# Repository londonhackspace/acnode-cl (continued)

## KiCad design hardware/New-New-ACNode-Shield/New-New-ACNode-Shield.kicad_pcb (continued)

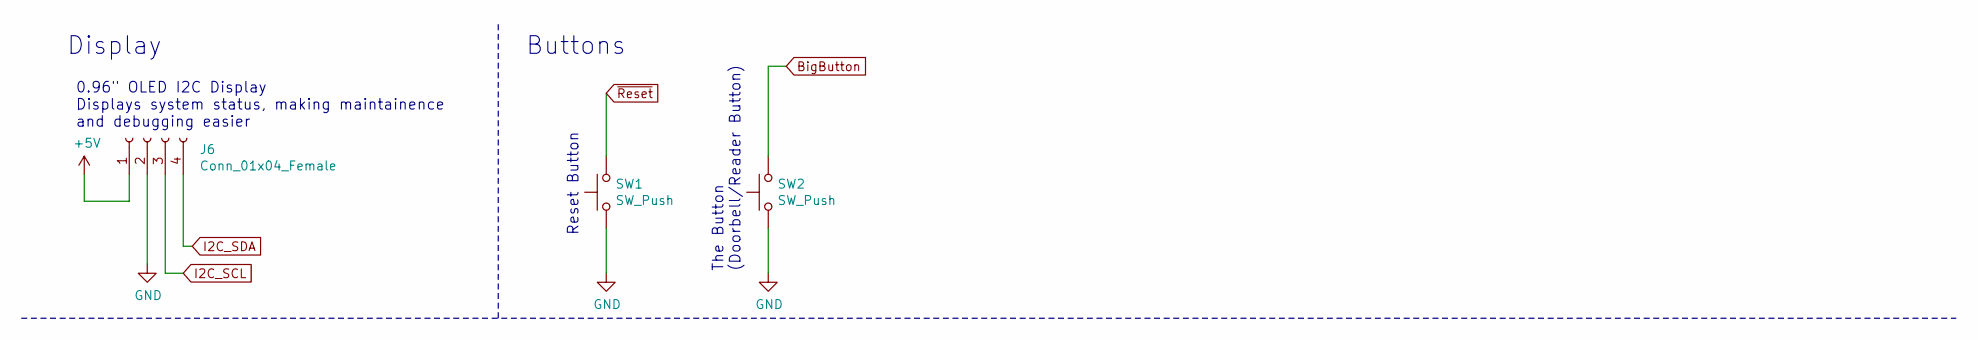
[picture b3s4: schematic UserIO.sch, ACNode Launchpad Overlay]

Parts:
J6: Conn_01x04_Female; PinHeader_1x04_P2.54mm_Vertical
SW1, SW2: SW_Push; SW_PUSH_6mm

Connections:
+5V: J6.1; also elsewhere on the board
BigButton: SW2.2; also elsewhere on the board
GND: J6.2, SW1.1, SW2.1; also elsewhere on the board
I2C_SCL: J6.3; also elsewhere on the board
I2C_SDA: J6.4; also elsewhere on the board
~Reset: SW1.2; also elsewhere on the board

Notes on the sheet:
Display
0.96" OLED I2C Display Displays system status, making maintainence and debugging easier
Buttons
Reset Button
The Button (Doorbell/Reader Button)

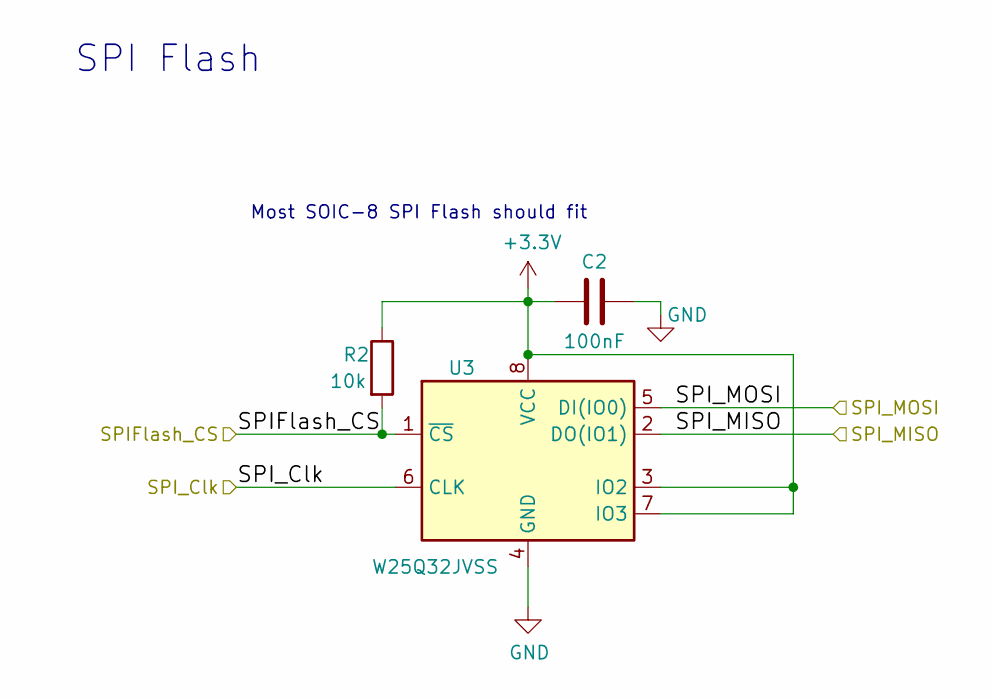
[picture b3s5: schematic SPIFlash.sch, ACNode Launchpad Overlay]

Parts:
C2: 100nF; C_0603_1608Metric
R2: 10k; R_0603_1608Metric
U3: W25Q32JVSS; SOIC-8_5.23x5.23mm_P1.27mm

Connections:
+3V3: C2.2, R2.1, U3.3 (IO2), U3.7 (IO3), U3.8 (VCC); also elsewhere on the board
/SPIFlash_CS: R2.2, U3.1 (~CS); also elsewhere on the board
/SPI_Clk: U3.6 (CLK); also elsewhere on the board
/SPI_MISO: U3.2 (DO(IO1)); also elsewhere on the board
/SPI_MOSI: U3.5 (DI(IO0)); also elsewhere on the board
GND: C2.1, U3.4 (GND); also elsewhere on the board

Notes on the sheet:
Most SOIC-8 SPI Flash should fit
SPI Flash

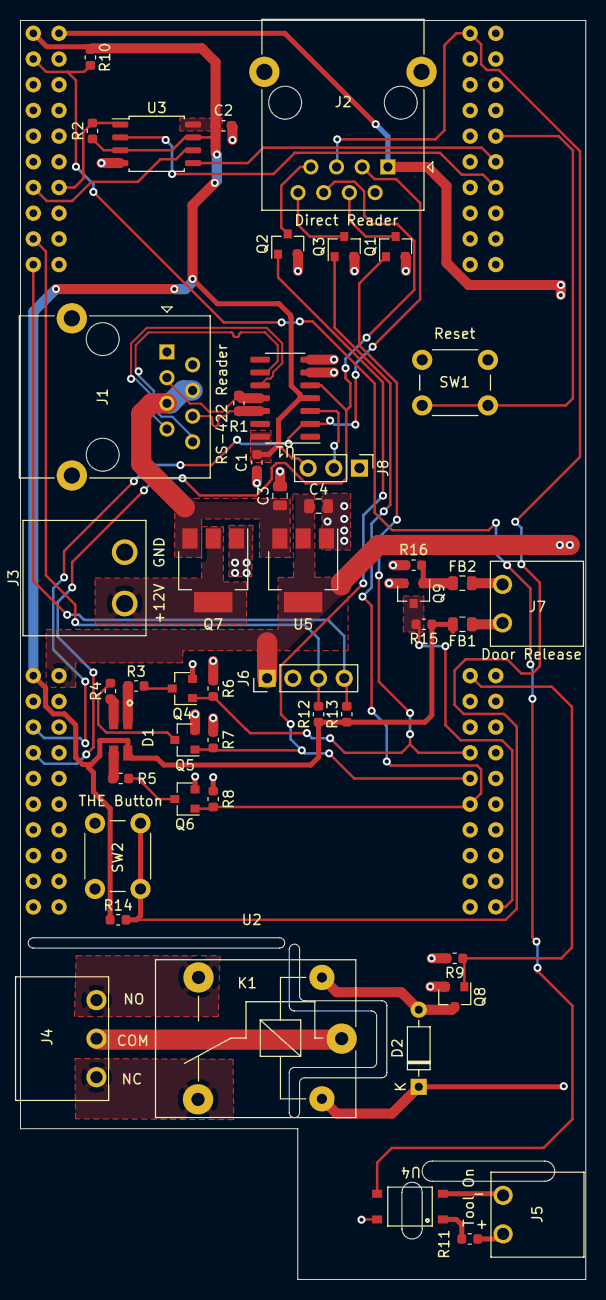
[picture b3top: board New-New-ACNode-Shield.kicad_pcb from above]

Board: 2 copper layers, 55.9 x 124.5 mm, 49 parts (0 on the bottom side), 45 nets.

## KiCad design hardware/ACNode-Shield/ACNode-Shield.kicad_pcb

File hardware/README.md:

# How to make an ACnode or Doorbot

Over the years the design of the ACnodes and doorbots have been gradually improved.

As of 2021-10-28, all acnodes and doorbots in London Hackspace have been using the 'New-ACNode-Doorbot-Shield' designs. This is a single PCB designed to
fit **underneath** a TI Tiva C XL Connected Launchpad microcrontroller board EK-TM4C1294XL EVAL BRD, TIVA C CONNECTED LAUNCHPAD. The Launchpad boards are normally available from Farnell and RS.

There are plans for an all-new doorbot/acnode board together with a reader module, but they are not as yet ready for use. This is to address interference on long cable runs between the acnode/doorbot board and reader.

The board features an on-board 5V coil relay that is suitable for switching up to 10A of 230V. If you need to switch anything greater, then use it to
energise the coil of an appropriate contactor.

Build up the ACnode board as per kicad schematics. On rev 1.1b, component values are silkscreened for easy assembly. You will require long header pins so that the Launchpad board sits above the relay. Hint when soldering the long header pins into this board - use a Launchpad upside-down as a jig to hold the pins, place the pins, place the ACnode board upside-down, then solder them. Once soldered, a blob of hot glue is advised to keep the long header pins spaced and prevent bending them when handling in future.
When building the board for the ACnode role, you may omit the LM7805 voltage regulator if you're only going to be providing it with +5V power.

Always ensure that any metal enclosure is suitably earthed.

## Doorbot role

You will require

- A +12V power supply, approximately 3A at 12V should be enough to energise a maglock or solenoid lock. You can't use POE for this, it won't provide enough current for a maglock.
- Optional: A sealed lead acid battery, recommended for exterior doors. The doorbot software is designed to handle power outages with no networking available.
- A suitable helpfully labelled DOOR EXIT button, SPDT or DPDT, must be able to handle the current of whatever lock you choose. We will use two poles to both interrupt the current to the lock (NC contact) and to signal the doorbot to hold the door open for a time.
- Some CAT5 or higher wiring and connectors to run a cable to the reader module.
- Some suitable wire. We've found that old +12V DC power cables for CCTV cameras is suitable for the 12V lock circuit.
- A suitable enclosure
- A micro-USB to laptop cable, of suitable length, for configuration and flashing the software.
- A maglock with bracket, or solenoid deadbolt. 12V DC.

## ACnode role

You will require

- A +5V power supply, most decent USB power supplies work well, and you can get POE splitters that will provide this via Micro USB as well. Most of the London Hackspace network switches support POE. This is normally the recommended solution.
- Some CAT5 or higher wiring and connectors to run a cable to the reader module.
- Knowledge of the tool that you are providing access control to. Ideally, you'd be switching a low(er) voltage control circuit like an e-stop, rather than turning full power on and off to the tool. For high current switching, use an external suitably sized mains contactor.
- optional: a tool-running input, like on the laser cutter, the AC node can log the time the tool was running.
- suitable enclosure, or suitable space within the tool for the board. DIN rail mounting is recommended, 3D printed DIN-rail clips have been known to work with the board glued to the clips. Where we need a standalone enclosure, we have used TA 241911 ENCLOSURE BOX, GREY, IP65, 240X191X107MM, Farnell Part number 1422671
- A micro-USB to laptop cable, of suitable length, for configuration and flashing the software.

Set the power select jumper on the Launchpad board to 'OTG', and plug your USB power supply into the 'OTG' interface, we'll use that to provide power to the microcontroller.

## Reader enclosure

Typically used for ACnode roles.
Can use any suitable enclosure, but ideally one deep enough for the arcade button, and a RJ45 modular connector. https://uk.farnell.com/schneider-electric/dpn10-10/box-abs-103x103x56mm/dp/161706 has worked well.
For a laser-cut card holder front-end, see the dxf files in this repository's hardware/ directory. These will need M2.5 nylon nuts to hold the stack of laser cut acrylic together through to the front cover of the reader.
We have typically used arcade microswitch buttons with LED. " Ultralux RGB Illuminated Arcade Button " from Arcade World UK. https://www.arcadeworlduk.com/products/ultralux-rgb-illuminated-arcade-button.html

For doorbot roles, we typically build the readers into standard socket boxes with blanking plates. Exterior card readers will need a suitably watertight enclosure with a watertight button.
Drilling a standard EN 60670-1 thermosetting plastic blanking plate to fit LED and buttons makes them prone to cracking. Start with a tiny pilot drill, ideally in a drill press, and work up sizes. Fortunately, they are cheap and very easy to come by (wilko,screwfix,B&Q).
RJ45 termination to a modular jack is typically within the enclosure rather than external as on most of the acnode role readers.
PN532 RFID reader module: Set to HSS mode. Elechouse V4. Order direct from Elechouse. Do not skimp on ordering from aliexpress or ebay, because there are huge numbers of clones with AWFUL antenna matching circuitry.

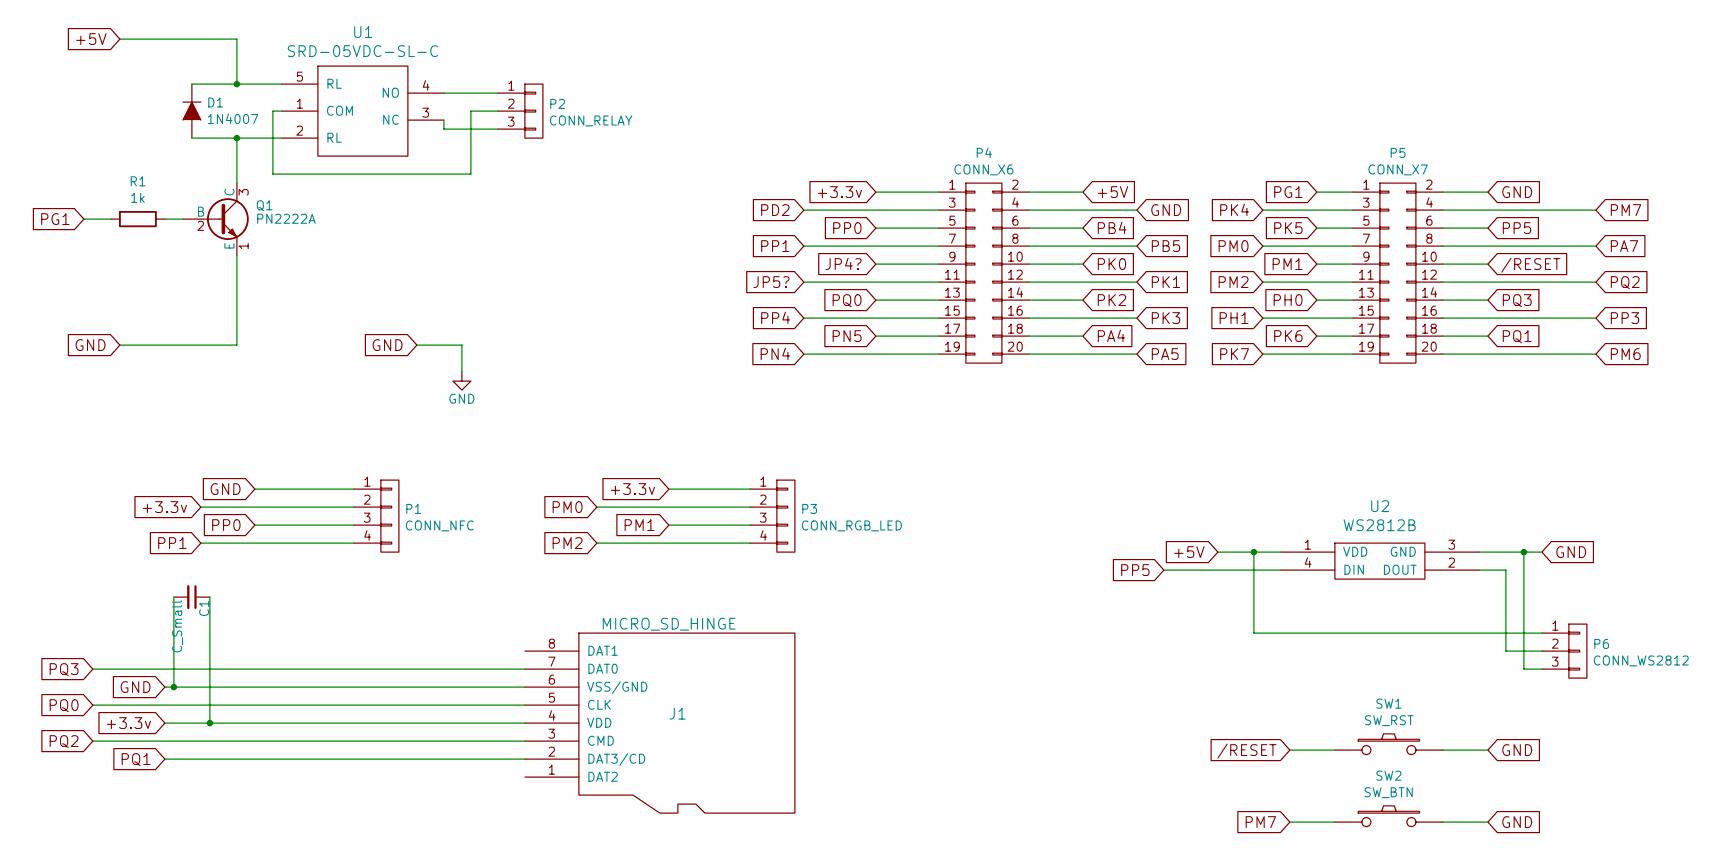
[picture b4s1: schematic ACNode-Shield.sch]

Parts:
C1: C_Small; C_1206
D1: 1N4007; Diode_DO-41_SOD81_Horizontal_RM10
J1: MICRO_SD_HINGE; MicroSD_Slot
P1: CONN_NFC; Pin_Header_Straight_1x04
P2: CONN_RELAY; TerminalBlock_Pheonix_MKDS1.5-3pol
P3: CONN_RGB_LED; Pin_Header_Straight_1x04
P4: CONN_X6; Socket_Strip_Straight_2x10
P5: CONN_X7; Socket_Strip_Straight_2x10
P6: CONN_WS2812; Pin_Header_Straight_1x03
Q1: PN2222A; TO-92_Inline_Wide
R1: 1k; Resistor_Horizontal_RM10mm
SW1: SW_RST; SW_PUSH_SMALL
SW2: SW_BTN; Socket_Strip_Straight_1x02
U1: SRD-05VDC-SL-C; Relay_SANYOU_SRD_Series_Form_C
U2: WS2812B; WS2812b

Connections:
+3.3v: C1.1, J1.4 (VDD), P1.2, P3.1, P4.1
+5V: D1.1 (K), P4.2, P6.1, U1.5 (RL), U2.1 (VDD)
/RESET: P5.10, SW1.1
GND: C1.2, J1.6 (VSS/GND), P1.1, P4.4, P5.2, P6.3, Q1.1 (E), SW1.2, SW2.2, U2.3 (GND)
JP4?: P4.9
JP5?: P4.11
unnamed: D1.2 (A), Q1.3 (C), U1.2 (RL)
unnamed: P2.1, U1.4 (NO)
unnamed: P2.2, U1.1 (COM)
unnamed: P2.3, U1.3 (NC)
unnamed: P6.2, U2.2 (DOUT)
unnamed: Q1.2 (B), R1.1
PA4: P4.18
PA5: P4.20
PA7: P5.8
PB4: P4.6
PB5: P4.8
PD2: P4.3
PG1: P5.1, R1.2
PH0: P5.13
PH1: P5.15
PK0: P4.10
PK1: P4.12
PK2: P4.14
PK3: P4.16
PK4: P5.3
PK5: P5.5
PK6: P5.17
PK7: P5.19
PM0: P3.2, P5.7
PM1: P3.3, P5.9
PM2: P3.4, P5.11
PM6: P5.20
PM7: P5.4, SW2.1
PN4: P4.19
PN5: P4.17
PP0: P1.3, P4.5
PP1: P1.4, P4.7
PP3: P5.16
PP4: P4.15
PP5: P5.6, U2.4 (DIN)
PQ0: J1.5 (CLK), P4.13
PQ1: J1.2 (DAT3/CD), P5.18
PQ2: J1.3 (CMD), P5.12
PQ3: J1.7 (DAT0), P5.14

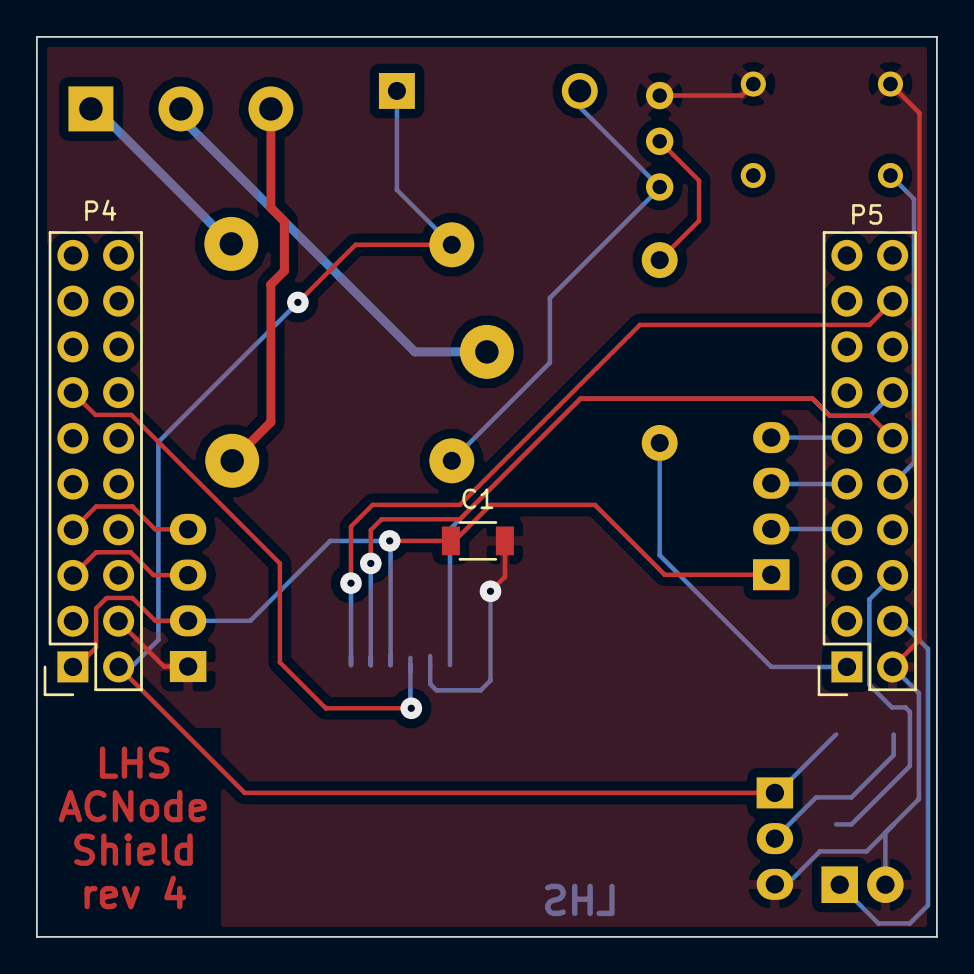
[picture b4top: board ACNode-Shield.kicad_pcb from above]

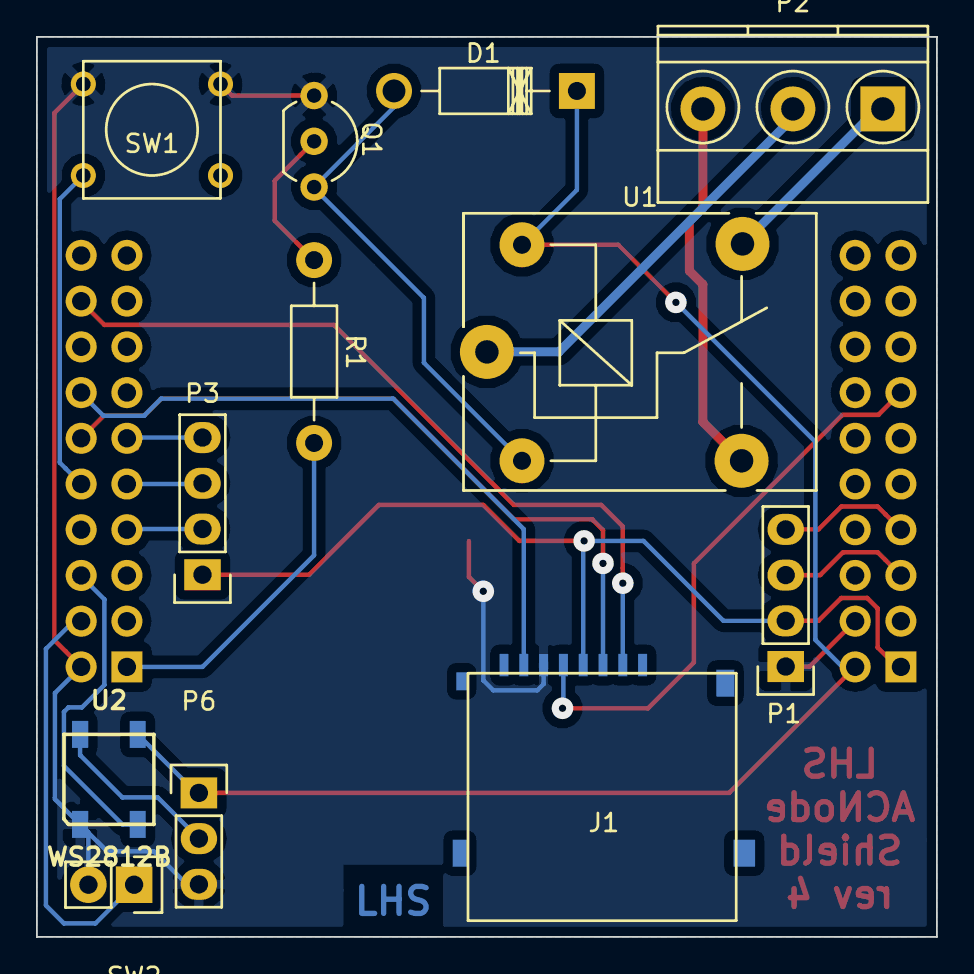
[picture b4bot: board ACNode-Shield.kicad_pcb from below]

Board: 2 copper layers, 50.0 x 50.0 mm, 15 parts (12 on the bottom side), 22 nets.

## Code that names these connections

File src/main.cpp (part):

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
Every am_i_alive(60000);

#define BUTTON_PIN PF_1
#define DOOR_RELEASE_PIN PM_6
#define SD_CS_PIN PC_7
#define ACNODE_DIR "ACNODE"

void serviceLed() { rgb.run(); };
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
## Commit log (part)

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2014-10-02 add a nice cli library (microrl, LGPLv3), add support for saving settings in the eeprom and editing them via the cli
2014-10-02 add support for saving status in the settings
2014-10-02 only count valid users
2014-10-07 get the mac address from the user registers, fixes #7, and fix a few more warnings
2014-10-07 a bit more helpful help
2014-10-09 also print the port
2014-10-10 only allow maintainers to run a tool if it's out of service.
2014-10-10 make the docs make a bit more sense
2014-11-13 add rgb support, reduce the grace period (it was annoyingly long)
2014-11-28 useful debugging thing
2014-11-28 Use a short timeout and the new PN532 powerdown thing so we can poll things faster.
    Use Every to not print debug out everytime.
    Still a work in progress, N.B. new version of the PN532 code needed (just git pull it).
2014-12-01 move the code that we call when we have a valid card code to it's own function.
    tidy things up a bit
    timeout adding a new card rather than waiting for ever.
    handle led's a bit better.
2014-12-03 keep state of what colour we are to avoid more flickering
2014-12-04 debounce a bit since we now sample the button much more often
2014-12-04 formatting
2014-12-14 switch the tool off when it is marked as out of service, bump to beta 2
2014-12-23 don't try to swith the tool on if it's out of service
2014-12-23 how to make the transistor switch and wire in the button
2014-12-29 poke the acserver with the tool run time
2014-12-31 better formatting
2015-02-19 if the board does not have valid settings, save the default ones. For some reason this makes the card reader work :/ see issue #15
2015-05-09 don't update the tool status on error
2015-05-09 print out the code version in a few places
2015-08-27 Door class for opening and closing the door.
2015-09-04 The SD card library is now found by Energia's compiler.
2015-09-05 Replaced code in user.cpp with calls to the SD card cache.
2015-09-08 toolUse is not used so remove it, fixes issue #31
2015-09-09 verify the user cache on startup (and with a command), closes #32
2015-09-10 Open door if a known card is presented. Parse numbers in http response, rather than a single digit. No caching at the moment.
2015-09-11 Add watchdog support, closes #17
2015-09-11 add a changelog
2015-09-12 add minimum on time support, closes #22
2015-09-12 bump version
2015-09-14 user.h -> card.h, bump version too
2015-09-15 get_user -> cache->get most of class Card, rest of code not converted yet
2015-09-22 add a cache type setting change some details in the settings struct - nodeid is now 16 bits upgrade settings if old settings found
2015-09-23 Fix issue with all cards appearing to have a long uid
2015-09-23 feed the watchdog in Cache::each
2015-09-24 more detail on hooking up an sdcard, add a cli command to change which cache to use
2015-09-26 Warn if the tool starts or stops running when it is switched off, fixes #37
2015-10-07 terminate the ret buffer to avoid printing junk when the network is down
2015-10-11 fix eepromcache not caching things
2015-11-05 Add an additional pin, negated, for use with a different type of a relay.
2016-04-12 Symbolic links to subtree'd PN532 library.
2016-04-12 Moved hardware directory to the root.
2016-04-12 Squashed 'lib/Syslog/' content from commit 1a11d1c
    git-subtree-dir: lib/Syslog
    git-subtree-split: 1a11d1cfe95d625688d14112cdd93d7c7566f6c3
2016-04-13 PlatformIO now has the latest Energia, but it still doesn't solve our problem with the SPI library.
2016-04-14 README
2016-04-18 Updated build recipe for travis. sigh.
2016-04-29 Added a pinout of the board in high res.
2016-05-07 PCB rev 1
2016-05-12 Removed a resistor, fixed some tracks.
2016-05-14 Removed old outputs.
2016-05-15 Design was mirrored, need to redo this whole thing from scratch.
2016-07-09 Don't die when there's no SD card connected.
2016-07-10 DRY, introduce timeout handling.
2016-07-10 Feed watchdogs here and there.
2016-07-10 Basic doorbot (1) now works.
2016-07-10 Announcing works, need to add card debouncing (?).
2016-07-10 Further changes - see last commit.
2016-07-10 Created a superclass with common logic, called Role.
2016-07-10 Fixed namespaced identifiers.
2016-07-11 "secret none" disables the secret key.
2016-09-29 I've made the component pads thicker, for easier soldering.
2016-10-04 Added some text on copper layers.
2016-11-04 Removed a single trace that wasn't needed.
2016-11-07 Very basic access control for the acnode - inefficient but simple.
2016-11-12 Got the LED to flash nicely.
2016-11-13 RGB class supports two-colour flashing. A maintainer can take a tool online and offline. When activated by a maintainer the LED turns yellow, when by a user - green.
2016-11-13 Correct colouring based on different user types.
2016-11-13 Tell acserver when the tool is in use.
2016-11-15 When retrieving a valid entry, bump the entry's expiration timestamp.
2016-11-17 If a card is cached already, don't add another entry.
2016-11-17 Tiny fix.
2016-11-23 Reversed contacts on the SD card connector - it should work now.
    Bumped revision of the board to 4.
2017-05-10 Added a rainbow cycle during bootup as a quick check if the LED is working.
    This relies on working OneMsTaskTimer.cpp implementation for which there will be a PR for in Energia.
2017-05-16 Folded user agent into a compile-time define.
2017-05-20 Check if tool is enabled, every 30 seconds - force-checking when disabled every 500ms doesn't make sense. The led lights up as red when it is out of order.
2017-05-20 Fix failing build. Included a patch that enables OneMsTaskTimer, a timer-based ticker for automatically updating the LED.
2018-08-04 Fixed build
2018-08-07 Fix key length in settings.cpp
2018-08-26 Add MQTT Announcer
    Added first pass at an MQTT announcer
2018-08-27 Turns out for reliable MQTT we need to yield regularly
2018-09-04 correct pin for DOOR_RELEASE_PIN
2018-09-08 bug on the popular AC node rev 2.0 board means that button_pin is now PF_1 instead of PM_7
2018-11-03 Modify RFID announcement over mqtt to include whether access was granted, or not.
2018-11-05 improve header file to reduce warnings at compile time
2018-11-24 Fix a couple of buffer overruns in the MQTT code
    One was the template class for the MQTT client was set to a maximum length of 50 bytes,
    which is shorter than most of our messages. The other was a more subtle one where the
    card buffer didn't have room for a null terminator.
2018-12-03 quick change of documentation, some clarification
2019-02-15 From Liam: The RFID card holders to be lasercut to hold the cards in the readers.
2019-02-28 fix bug where the verify() call wasn't actually touching datestamp in ramcache.
2019-03-01 Improve cacheing refresh, implement colour code MAUVE that means that the card has been read, and it's waiting on a network response. If this colour stays on, it means that there's a networking probl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
2019-03-10 Make more robust in cases of network link failure
    When the network link goes down, the doorbot tries
    to do stuff anyway, which results in a generally nasty situation
    where it will probably hit enough timeouts to trigger the watchdog.
    This is bad because hitting the watchdog timer clears the cache, meaning
    people who otherwise would have been permitted access now are not.
    This commit adds checking of link status to a few key places. It's only
2019-03-10 Fix build fail on doorbot_ac
2019-03-18 report tool relay turned off; this wasn't working properly, and acserver wasn't getting notified of end of regular acnode session.
2019-04-04 start up is rainbow cycling
2019-04-05 Update README.md
    remove platformio build instructions
2019-07-08 Fixed travis syntax (hopefully)
2019-07-10 Move announcer run() call to main.cpp
    Since we're using announcers on tools as well now, it makes more sense to do this in one place.
2019-07-12 Add git SHA to startup MQTT message
    Currently, the message on startup shows node version, which doesn't
    change nearly as much as the git sha, so this commit adds support for
    logging git sha.
2019-07-20 Cache: Make pure virtual
    By making the Cache class pure virtual, and adding an extra layer CacheBase
    for the common logic, it becomes possible to compose cache objects
    (coming to a commit history near you soon)
2019-07-25 Add settings version to MQTT messages
    The idea here being that in future, it will be possible to get a good idea
    what nodes are on what settings version, and hence, what versions are actually
    still in use, and hence, which migration paths need to exist
2019-08-20 Fixed up compiler options to show warnings for some parts of the code
    For now, continuing to hide them in the library code.
2019-08-21 A little rework and more get endpoints
2019-09-07 got maintainer cache function working
2019-09-10 Stop the EEProm cache from "borrowing" storage from the config
    The eeprom cache iteration logic contained a while(1) and no regard for the end of the eeprom. This results
    in it wrapping around, and trying to use the config as a card record, which, with validation, ends up modifying the
    config to make it no longer config. This is most unhelpful.
    This commit adds actual bounds validation to the EEProm cache logic. Novel idea, I know.
2019-09-22 add boolean field to exit announcement, as per mich181189's suggestion
2020-08-25 Update docs feed the watchdog if you're typing commands set tool run start time by default to tool enabled time, which might help to prevent excessive tool run time
2021-02-28 Updated Energia core
2021-03-21 Added SPI Flash caching support
2021-03-21 Prepare for the addition of remote LEDs
    Unlike the card reader, when we're using a remote LED interface, we
    still want to light the local LEDs. Because of this, this commit adds
    the ability to *also* send LED data elsewhere.
2021-03-24 Bug Fixes
    Small fixes
2021-07-25 Detect Card Reader Faults
    The announcer now checks to see if the card reader is present, by
    reading the firmware version. If it is not present, it changes the text
    of the ALIVE is changed to reveal this fault.
2021-07-25 Add option to invert colours
    Current hardware requires driving the LED lines low to turn them on. The
    code therefore specifies all colours inverted.
    This method of driving the active low pins makes little sense, and more
    to the point, is incompatible with the newer hardware design, which uses
    buffer transistors to allow an on-board LED to be driven in parallel
    without loading the external LED.
2021-07-25 Try not building on a dinosaur of a distro...
2021-11-12 1.1b of Dawid's design, some cosmetic changes only.
2021-11-18 Add watchdog reset to verify loop
2021-11-23 DIN Rail clip.stl, based on github.com:Laser4DIY/Laser4DIY_Enclosure via openscad
2021-12-01 slight tweak to give better clamping when printed with PLA. 0.5mm tighter.
2022-03-01 improve documentation a little.
2022-04-07 internal measurements
2022-04-18 Update readme.md
    Errata on silkscreen
2024-12-09 Added generated hardware files to .gitignore
2024-12-09 Cleaned up const char* to char* warnings
2024-12-09 Fixed signed/unsigned comparison warnings and "next = ++next" ambiguity
2025-03-01 Added a one second second delay on card removal. This is to counter some cards which repeatedly disconnect the reconnect.
